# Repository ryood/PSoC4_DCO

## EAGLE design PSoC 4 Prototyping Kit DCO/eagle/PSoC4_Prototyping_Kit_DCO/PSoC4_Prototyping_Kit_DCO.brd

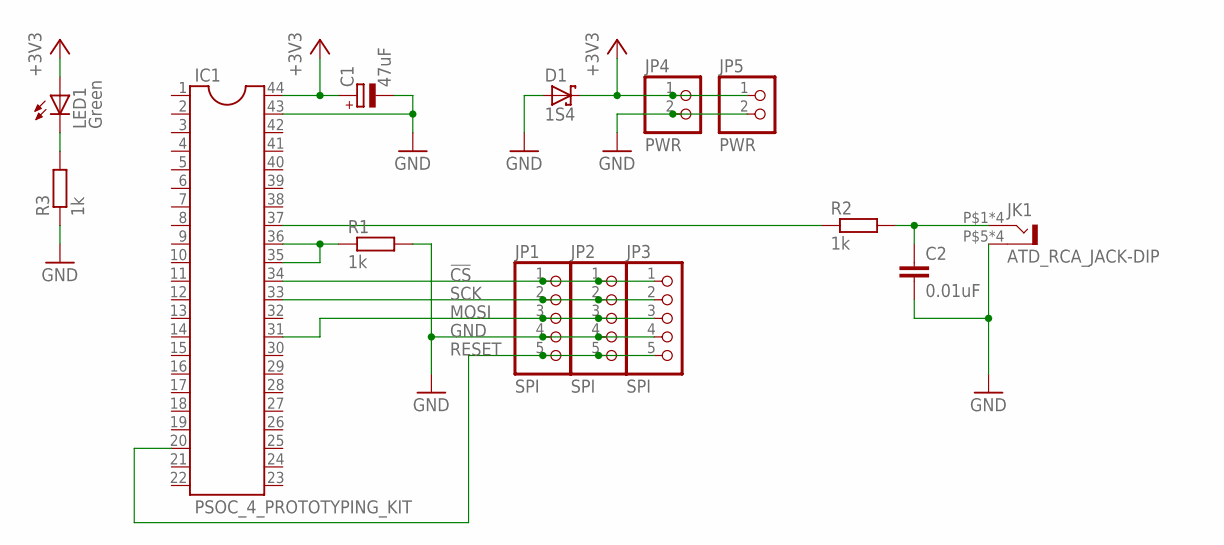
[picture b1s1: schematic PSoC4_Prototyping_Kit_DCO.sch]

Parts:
C1: 47uF; E2,5-5
C2: 0.01uF; C050-024X044
D1: 1S4; DO35-7
IC1: PSOC_4_PROTOTYPING_KIT; DIL44-8
JK1: ATD_RCA_JACK-DIP; ATD_RCA_JACK_DIP
JP1, JP2, JP3: SPI; 1X05
JP4, JP5: PWR; 1X02
LED1: Green; LED3MM
R1, R2, R3: 1k; 0207/7

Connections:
!CS: IC1.34, JP1.1, JP2.1, JP3.1
+3V3: C1.+, D1.C, IC1.44, JP4.1, JP5.1, LED1.A
GND: C1.-, C2.2, D1.A, IC1.43, JK1.P$5 (S), JK1.P$6 (S), JK1.P$7 (S), JK1.P$8 (S), JP1.4, JP2.4, JP3.4, JP4.2, JP5.2, R1.2, R3.1
MOSI: IC1.31, JP1.3, JP2.3, JP3.3
unnamed: IC1.35, IC1.36, R1.1
unnamed: LED1.K (C), R3.2
unnamed: IC1.37, R2.1
unnamed: C2.1, JK1.P$1 (T), JK1.P$2 (T), JK1.P$3 (T), JK1.P$4 (T), R2.2
RESET: IC1.20, JP1.5, JP2.5, JP3.5
SCK: IC1.33, JP1.2, JP2.2, JP3.2

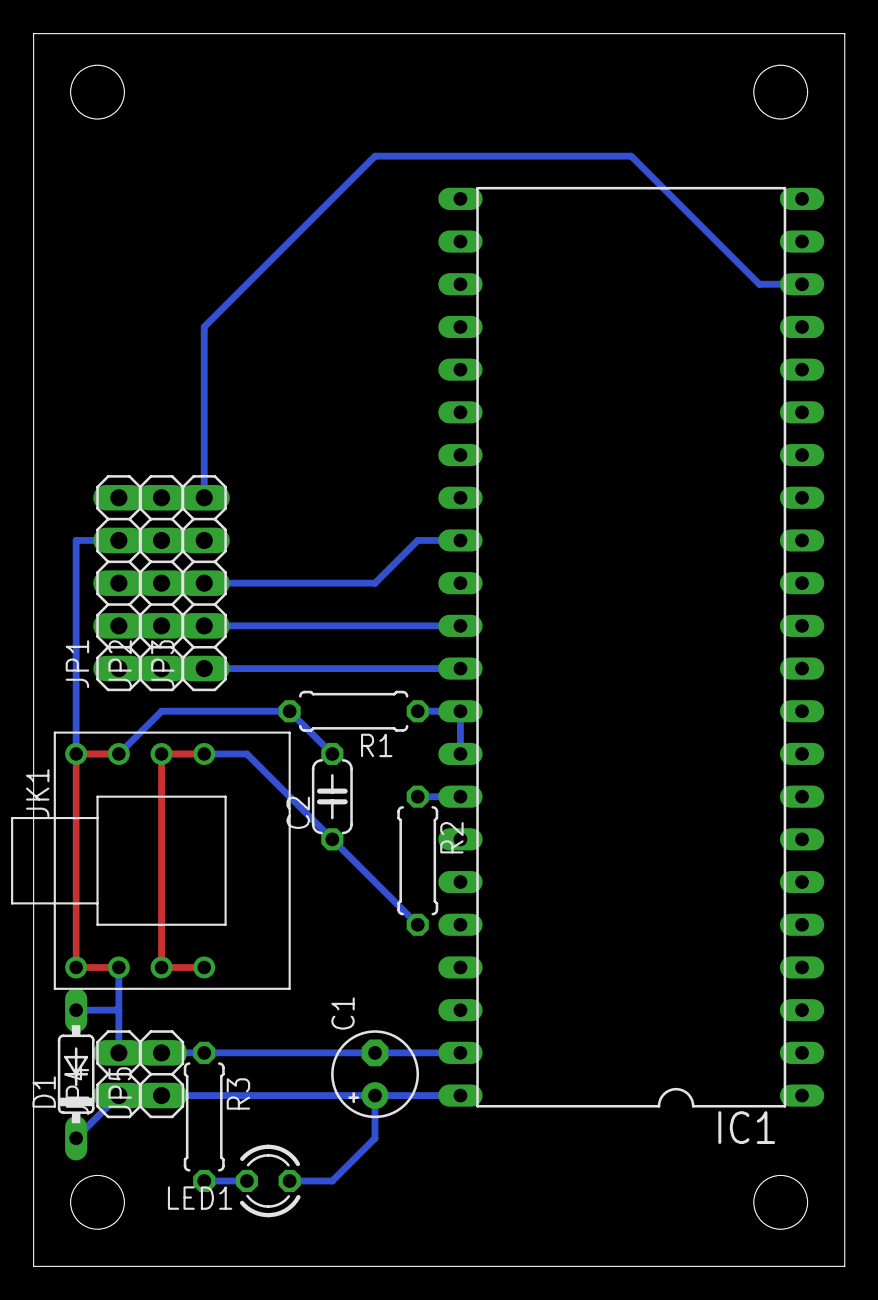
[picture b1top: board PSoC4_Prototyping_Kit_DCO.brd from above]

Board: 2 copper layers, 48.2 x 73.3 mm, 14 parts (0 on the bottom side), 10 nets.

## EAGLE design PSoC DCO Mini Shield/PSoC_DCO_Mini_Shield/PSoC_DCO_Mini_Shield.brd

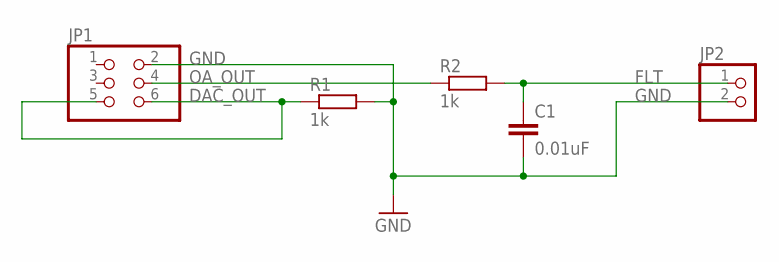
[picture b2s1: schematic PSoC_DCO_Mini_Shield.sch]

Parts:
C1: 0.01uF; C025-025X050
JP1: PINHD-2X3; 2X03
JP2: PINHD-1X2; 1X02
R1, R2: 1k; 0207/7

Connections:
DAC_OUT: JP1.5, JP1.6, R1.1
FLT: C1.1, JP2.1, R2.2
GND: C1.2, JP1.2, JP2.2, R1.2
OA_OUT: JP1.4, R2.1

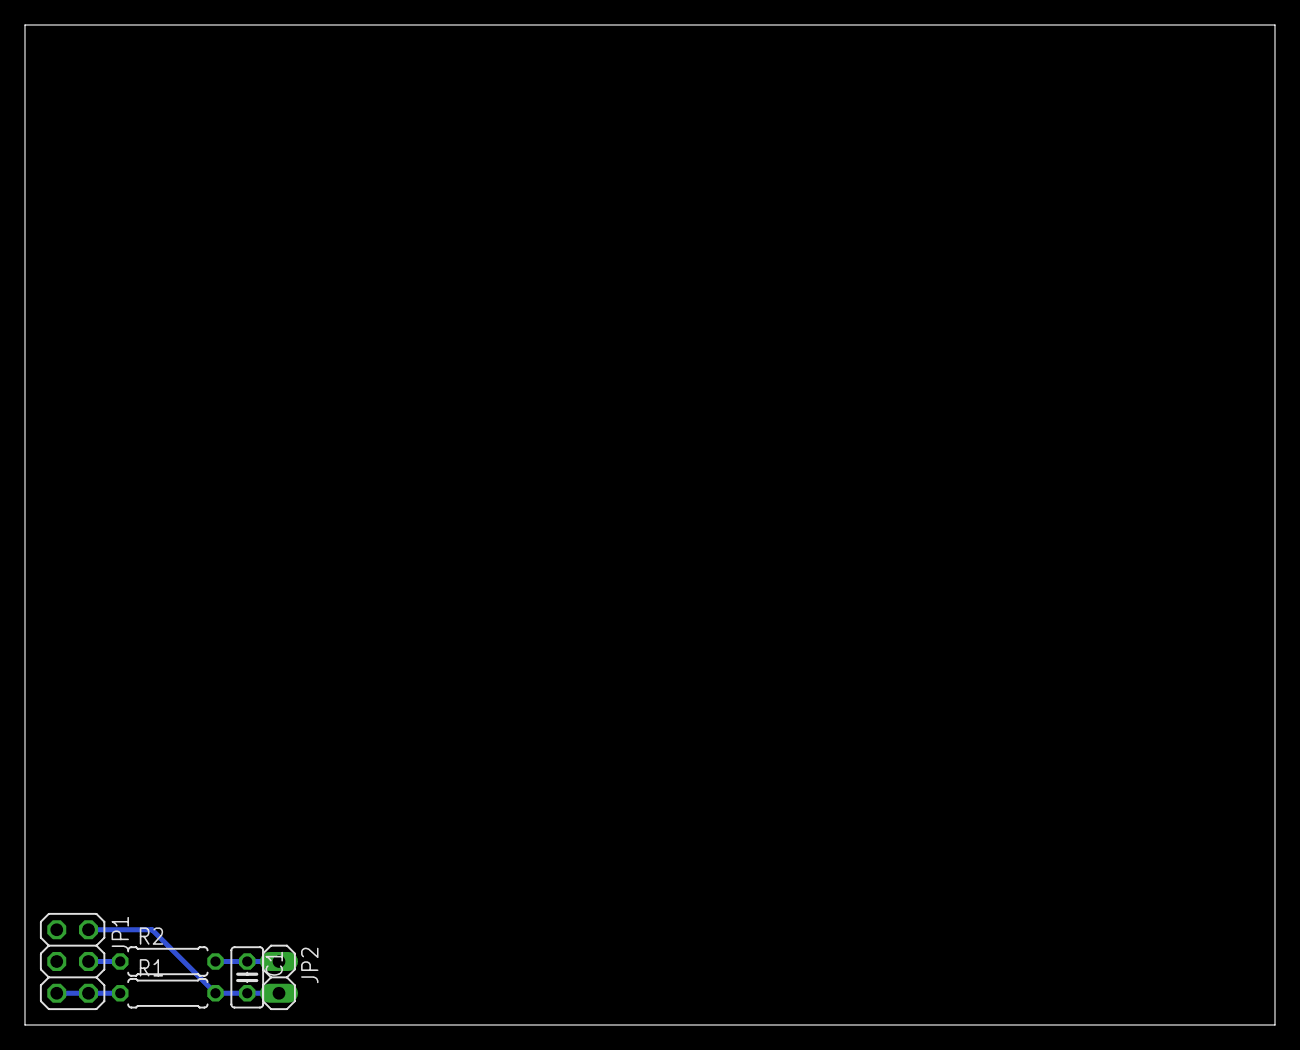
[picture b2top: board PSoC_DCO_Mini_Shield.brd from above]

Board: 2 copper layers, 100.0 x 80.0 mm, 5 parts (0 on the bottom side), 4 nets.

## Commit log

2016-05-07 Impl: Square Wave
2016-05-07 Impl: Square Wave Duty
2016-05-11 Add: PSoC4_SPI_Slave_Test Project
2016-05-11 音声再生（1/2周波数）
2016-05-11 音声再生（サンプルング周波数12MHz）
2016-05-11 ソースコードを整理
2016-05-11 DCOのUIを追加
2016-05-14 ソースを整理
2016-05-14 Project PSoC4_DCO_for_Arduino_Sequencer_Nokia5110を追加
2016-05-14 SPIクロックを8MHzに設定
2016-06-03 Add: PSoC4_DCO_for_NucleoF401RE Project
2016-06-03 PSoC4_DCO_for_NucleoF401RE IDAC8で実装 シーケンサー: https://developer.mbed.org/users/ryood/code/SpiSequenceSender_Test/
2016-06-03 timePeriodの計算をuint64に拡張
2016-06-03 #defineでUART/LCDを切り替えられるように変更
2016-06-06 Add: PSoC4_DCO_for_NucleoF401RE_Interrupt_Test Project (Internal Interrupt)
2016-06-06 doCommand()の位置を修正
2016-06-09 Add: PSoC4_DCO_No_SPI_Interrupt_Test Project
2016-06-09 波形の開始地点でTimerのPeriodを変更するように修正
2016-06-09 ソースコードを修正
2016-06-09 5m秒間隔で割り込み。STEPごとの周波数をTie
2016-06-09 波形の開始地点でTimer_SamplingのPeriodを変更するように修正
2016-06-12 割みベクタの変更をISR_Timer_Sampling_SetVector()に変更
2016-06-26 PSoC4_DCO_for_NucleoF401RE_Interrupt_Test.cydsn: IDAC8の出力を0-306uAに変更
2016-07-18 NucleoシーケンサーとDCO、DCF、DCFの結合テスト（UIなし）
2016-07-19 unit test begin
2016-07-19 Init: 440Hz, saw_wave
2016-07-19 change TITLE_STR
2016-08-02 SPIのピンアサインを変更。UART CharLCDをdisable
2016-08-02 Add: PSoC DCO Mini Shield
2016-09-09 Add: PSoC4PrototypingKit_DCO.cydsn Project
2016-09-11 Assign: mosi:P0[4] sclk:P0[6] ss:P0[7]
2016-09-14 Add: PSoC 4 Prototyping Kit DCO & Files
2016-10-20 move local directory
2016-10-20 Add a inverse Diode from VDD to GND
2016-10-20 Update: png files (eagle)
2016-11-20 Add: Reset Line
2017-05-07 Before Impl. Triangle Wave
2017-05-07 Pulse Width Control: Saw <-> Triangle
